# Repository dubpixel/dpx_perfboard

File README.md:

<!-- Improved compatibility of back to top link: See: https://github.com/othneildrew/Best-README-Template/pull/73 -->

<!--
*** Thanks for checking out the Best-README-Template. If you have a suggestion
*** that would make this better, please fork the repo and create a pull request
*** or simply open an issue with the tag "enhancement".
*** Don't forget to give the project a star!
*** Thanks again! Now go create something AMAZING! :D

*** /// d   u   b   p   i   x   e   l  ---  f   o   r   k   ////--
*** this has additionally been modifed by @dubpixel for hardware use
*** search dpx_perfboard.. search & replace is COMMAND OPTION F
*** 
*** todo: want to add reflections seciton, upload as github template.  - done 12.9
*** todo: backport to blank template - done 12.9**
*** todo add small product image thats not in a details tag
*** figure out how to get the details tag to properly render in jekyll for gihub pages.

-->

<!-- PROJECT SHIELDS -->
<!--
*** I'm using markdown "reference style" links for readability.
*** Reference links are enclosed in brackets [ ] instead of parentheses ( ).
*** See the bottom of this document for the declaration of the reference variables
*** for contributors-url, forks-url, etc. This is an optional, concise syntax you may use.
*** https://www.markdownguide.org/basic-syntax/#reference-style-links
***
-->
[![Contributors][contributors-shield]][contributors-url]
[![Forks][forks-shield]][forks-url]
[![Stargazers][stars-shield]][stars-url]
[![Issues][issues-shield]][issues-url]
[![MIT License][license-shield]][license-url]
[![LinkedIn][linkedin-shield]][linkedin-url]

<!-- PROJECT LOGO -->
<br />
<div align="center">

<h1 align="center">dpx_perfboard</h1>
<h3 align="center"><i>_yes... it comes in black!_</i></h3>
<br />
  <p align="center">
    ...an open source kicad protoboard in various sizes for whatever!
        <br />
    <p align="center">
     <a href="https://github.com/dubpixel/dpx_perfboard/tree/main/"><strong>Project Here!</strong></a>
     »  
    <a href="https://github.com/dubpixel/dpx_perfboard/tree/main/src/bom"><strong>BOM Here!</strong></a>
     » 
    <a href="https://dubpixel.github.io/dpx_perfboard/ebom/index.html"><strong>Interactive BOM Here!</strong></a>
     <br />
    <a href="https://github.com/dubpixel/dpx_perfboard/issues/new?labels=bug&template=bug-report---.md">Report Bug</a>
    ·
    <a href="https://github.com/dubpixel/dpx_perfboard/issues/new?labels=enhancement&template=feature-request---.md">Request Feature</a>
    </div>
    </p>
</div>
   <br />
<!-- TABLE OF CONTENTS -->
<details>
  <summary>Table of Contents</summary>
  <ol>
    <li>
      <a href="#about-the-project">About The Project</a>
      <ul>
        <li><a href="#built-with">Built With</a></li>
      </ul>
    </li>
    <li>
      <a href="#getting-started">Getting Started</a>
      <ul>
        <li><a href="#prerequisites">Prerequisites</a></li>
        <li><a href="#installation">Installation</a></li>
      </ul>
    </li>
    <li><a href="#usage">Usage</a></li>    
    <li><a href="#reflection">Reflection</a></li>
    <li><a href="#roadmap">Roadmap</a></li>
    <li><a href="#contributing">Contributing</a></li>
    <li><a href="#license">License</a></li>
    <li><a href="#contact">Contact</a></li>
    <li><a href="#acknowledgments">Acknowledgments</a></li>
  </ol>
</details>
    <br />
<!-- ABOUT THE PROJECT -->
</div>

## About The Project
i needed to have a perfboard spacing to test in kicad for another project so naturally i decided to just finish it off. Nice to have some dpx perfboards with added busses, our logo, and all black .

author(s): // www.dubpixel.tv  - i@dubpixel.tv | other authors

<details>
  <summary>Images</summary>
  
### 05x10+SMT 
![FRONT][product-a]

### 05x15
![FRONT][product-b]

### 05x30-split
![FRONT][product-c]

</details>

<p align="right">(<a href="#readme-top">back to top</a>)</p>

### Built With 
 * [![KiCad][KiCad.org]][KiCad-url]
<!--
  
 * [![Fusion360][Fusion-360]][Autodesk-url]
 * [![Next][Next.js]][Next-url]
 * [![React][React.js]][React-url]
 * [![Vue][Vue.js]][Vue-url]
 * [![Angular][Angular.io]][Angular-url]
 * [![Svelte][Svelte.dev]][Svelte-url]
 * [![Laravel][Laravel.com]][Laravel-url]
 * [![Bootstrap][Bootstrap.com]][Bootstrap-url]
 * [![JQuery][JQuery.com]][JQuery-url]
 
-->
<p align="right">(<a href="#readme-top">back to top</a>)</p>

<!-- GETTING STARTED -->
## Getting Started

### Prerequisites

### Installation

1. Download...
2. Enjoy.
3. Repeat as Needed!

<p align="right">(<a href="#readme-top">back to top</a>)</p>

<!-- USAGE EXAMPLES -->
## Usage

<!-- Use this space to show useful examples of how a project can be used. Additional screenshots, code examples and demos work well in this space. You may also link to more resources.

_For more examples, please refer to the [Documentation](https://example.com)_-->

<p align="right">(<a href="#readme-top">back to top</a>)</p>

## Reflection
<!-- 
* what did we learn? 
* what do we like/hate?
* what would/could we do differently? 
-->

<p align="right">(<a href="#readme-top">back to top</a>)</p>

<!-- ROADMAP -->

## Roadmap

- [ ] Feature 1
    - [ ] Nested Feature

See the [open issues](https://github.com/dubpixel/dpx_perfboard/issues) for a full list of proposed features (and known issues).

<p align="right">(<a href="#readme-top">back to top</a>)</p>

<!-- CONTRIBUTING -->
## Contributing

Contributions are what make the open source community such an amazing place to learn, inspire, and create. Any contributions you make are **greatly appreciated**.

If you have a suggestion that would make this better, please fork the repo and create a pull request. You can also simply open an issue with the tag "enhancement".
Don't forget to give the project a star! Thanks again!

1. Fork the Project
2. Create your Feature Branch (`git checkout -b feature/AmazingFeature`)
3. Commit your Changes (`git commit -m 'Add some AmazingFeature'`)
4. Push to the Branch (`git push origin feature/AmazingFeature`)
5. Open a Pull Request

<p align="right">(<a href="#readme-top">back to top</a>)</p>

### Top contributors:

<!-- LICENSE -->
## License

  Distributed under the UNLICENSE License. See `LICENSE.txt` for more information.

<p align="right">(<a href="#readme-top">back to top</a>)</p>

<!-- CONTACT -->
## Contact

  ### Joshua Fleitell - i@dubpixel.tv

  Project Link: [https://github.com/dubpixel/dpx_perfboard](https://github.com/dubpixel/dpx_perfboard)

<p align="right">(<a href="#readme-top">back to top</a>)</p>

<!-- ACKNOWLEDGMENTS -->
## Acknowledgments

<!--
  *  - the best !
-->

<p align="right">(<a href="#readme-top">back to top</a>)</p>

<!-- MARKDOWN LINKS & IMAGES -->
<!-- https://www.markdownguide.org/basic-syntax/#reference-style-links -->
[contributors-shield]: https://img.shields.io/github/contributors/dubpixel/dpx_perfboard.svg?style=for-the-badge
[contributors-url]: https://github.com/dubpixel/dpx_perfboard/graphs/contributors
[forks-shield]: https://img.shields.io/github/forks/gdubpixel/dpx_perfboard.svg?style=for-the-badge
[forks-url]: https://github.com/dubpixel/dpx_perfboard/network/members
[stars-shield]: https://img.shields.io/github/stars/dubpixel/dpx_perfboard.svg?style=for-the-badge
[stars-url]: https://github.com/dubpixel/dpx_perfboard/stargazers
[issues-shield]: https://img.shields.io/github/issues/dubpixel/dpx_perfboard.svg?style=for-the-badge
[issues-url]: https://github.com/dubpixel/dpx_perfboard/issues
[license-shield]: https://img.shields.io/github/license/dubpixel/dpx_perfboard.svg?style=for-the-badge
[license-url]: https://github.com/dubpixel/dpx_perfboard/blob/master/LICENSE.txt
[linkedin-shield]: https://img.shields.io/badge/-LinkedIn-black.svg?style=for-the-badge&logo=linkedin&colorB=555
[linkedin-url]: https://linkedin.com/in/jfleitell
[product-screenshot]: images/screenshot.png
[product-front]: images/front.png
[product-rear]: images/rear.png
[product-pcbFront]: images/pcb_front.png
[product-pcbRear]: images/pcb_rear.png
[product-a]: images/5x10.png
[product-b]: images/5x15.png
[product-c]: images/5x30s.png
[Next.js]: https://img.shields.io/badge/next.js-000000?style=for-the-badge&logo=nextdotjs&logoColor=white
[Next-url]: https://nextjs.org/
[React.js]: https://img.shields.io/badge/React-20232A?style=for-the-badge&logo=react&logoColor=61DAFB
[React-url]: https://reactjs.org/
[Vue.js]: https://img.shields.io/badge/Vue.js-35495E?style=for-the-badge&logo=vuedotjs&logoColor=4FC08D
[Vue-url]: https://vuejs.org/
[Angular.io]: https://img.shields.io/badge/Angular-DD0031?style=for-the-badge&logo=angular&logoColor=white
[Angular-url]: https://angular.io/
[Svelte.dev]: https://img.shields.io/badge/Svelte-4A4A55?style=for-the-badge&logo=svelte&logoColor=FF3E00
[Svelte-url]: https://svelte.dev/
[Laravel.com]: https://img.shields.io/badge/Laravel-FF2D20?style=for-the-badge&logo=laravel&logoColor=white
[Laravel-url]: https://laravel.com
[Bootstrap.com]: https://img.shields.io/badge/Bootstrap-563D7C?style=for-the-badge&logo=bootstrap&logoColor=white
[Bootstrap-url]: https://getbootstrap.com
[JQuery.com]: https://img.shields.io/badge/jQuery-0769AD?style=for-the-badge&logo=jquery&logoColor=white
[JQuery-url]: https://jquery.com 
[KiCad.org]: https://img.shields.io/badge/KiCad-v8.0.6-blue
[KiCad-url]: https://kicad.org 
[Fusion-360]: https://img.shields.io/badge/Fusion360-v4.2.0-green
[Autodesk-url]: https://autodesk.com

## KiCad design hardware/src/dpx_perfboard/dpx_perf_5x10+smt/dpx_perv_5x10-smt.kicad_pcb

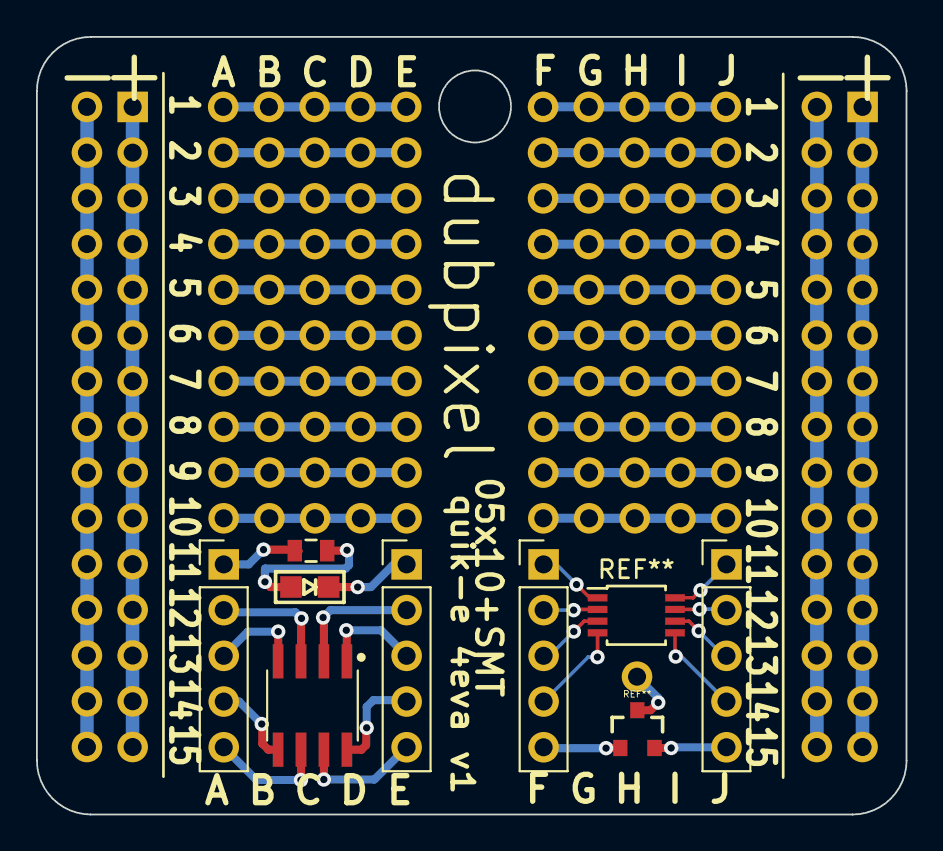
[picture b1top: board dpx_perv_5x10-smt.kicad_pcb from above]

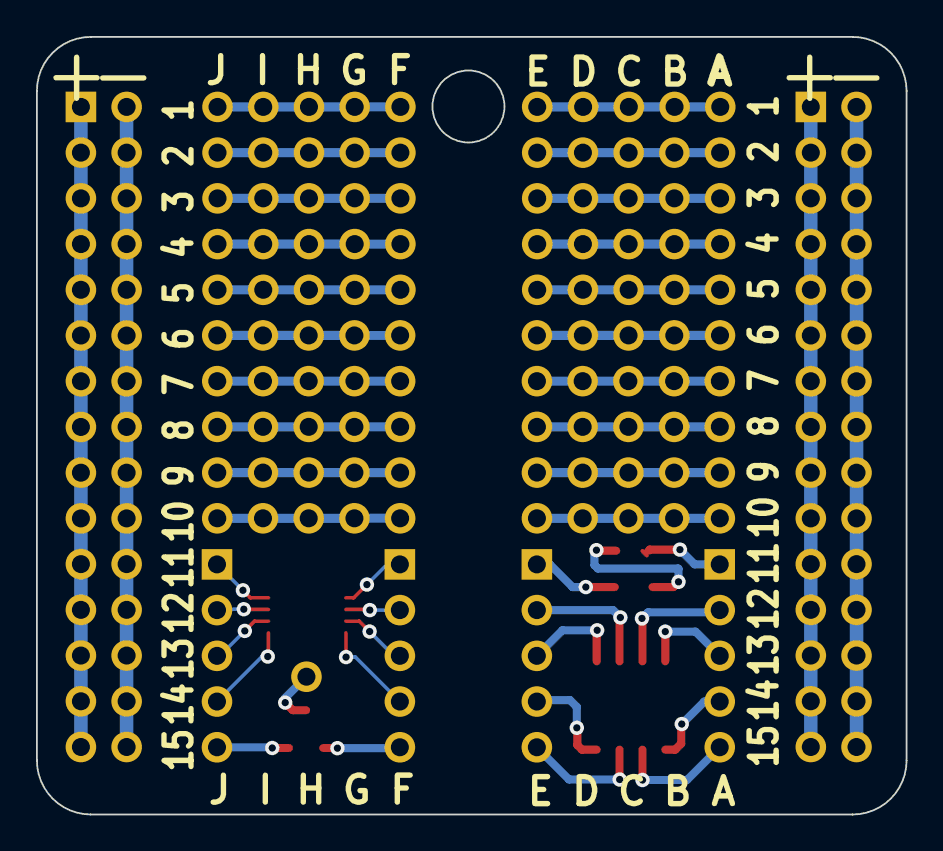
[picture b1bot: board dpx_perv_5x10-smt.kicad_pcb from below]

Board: 4 copper layers, 48.3 x 43.2 mm, 5 parts (2 on the bottom side), 2 nets.

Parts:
1: SOIC127P600X144-8
J1: Conn_02x10_Top_Bottom; dpx-02x15-nosilk
J2: Conn_02x30_Top_Bottom; dpx-02x15-nosilk
U1, U2: DPX_PROTOBOARD-5x5

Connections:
GND: J1.2, J1.4, J1.6, J1.8, J1.10, J1.12, J1.14, J1.16, J1.18, J1.20, J2.2, J2.4, J2.6, J2.8, J2.10, J2.12, J2.14, J2.16, J2.18, J2.20
VCC: J1.1, J1.3, J1.5, J1.7, J1.9, J1.11, J1.13, J1.15, J1.17, J1.19, J2.1, J2.3, J2.5, J2.7, J2.9, J2.11, J2.13, J2.15, J2.17, J2.19

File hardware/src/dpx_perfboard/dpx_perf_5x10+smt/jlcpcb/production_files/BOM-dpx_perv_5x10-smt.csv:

Comment,Designator,Footprint,LCSC
Conn_02x10_Top_Bottom,J1,dpx-02x15-nosilk,
Conn_02x30_Top_Bottom,J2,dpx-02x15-nosilk,
~,U2,DPX_PROTOBOARD-5x5,
~,U1,DPX_PROTOBOARD-5x5,

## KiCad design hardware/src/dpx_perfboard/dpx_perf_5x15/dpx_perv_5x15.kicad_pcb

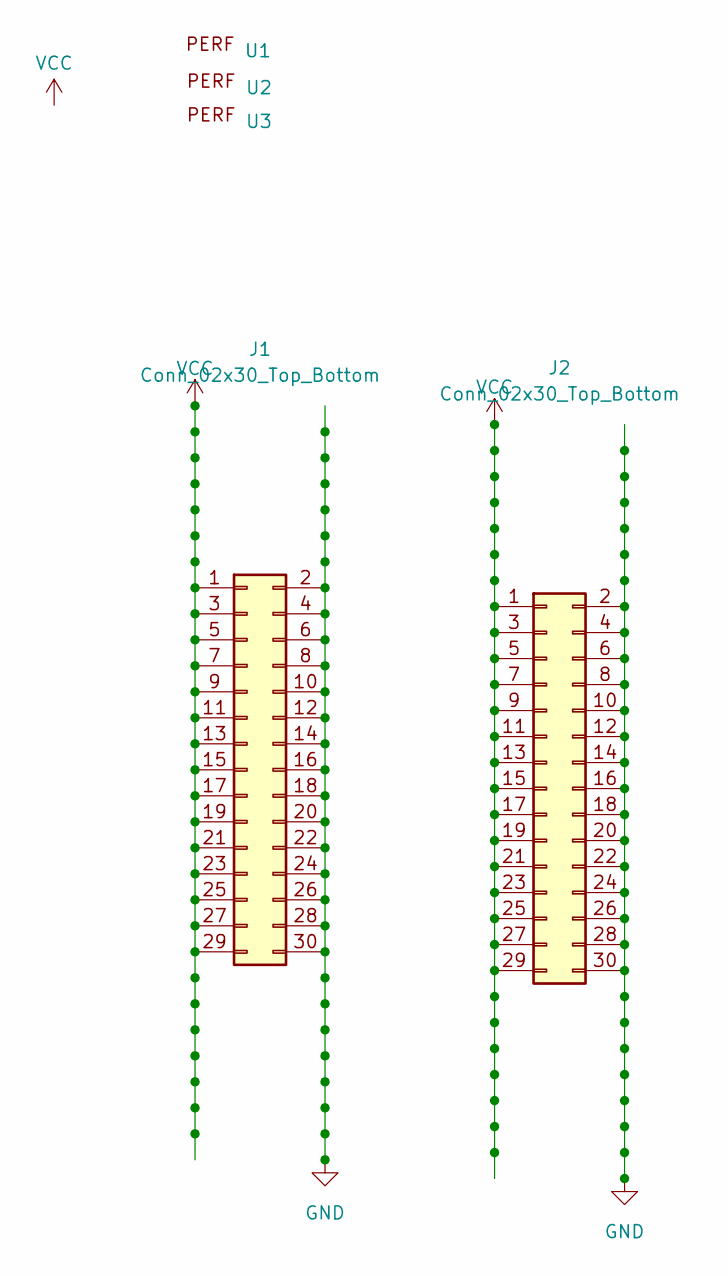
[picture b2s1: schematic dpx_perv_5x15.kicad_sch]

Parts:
J1, J2: Conn_02x30_Top_Bottom; dpx-02x15-nosilk
U1, U2, U3: DPX_PROTOBOARD-5x5

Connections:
GND: J1.2, J1.4, J1.6, J1.8, J1.10, J1.12, J1.14, J1.16, J1.18, J1.20, J1.22, J1.24, J1.26, J1.28, J1.30, J2.2, J2.4, J2.6, J2.8, J2.10, J2.12, J2.14, J2.16, J2.18, J2.20, J2.22, J2.24, J2.26, J2.28, J2.30
VCC: J1.1, J1.3, J1.5, J1.7, J1.9, J1.11, J1.13, J1.15, J1.17, J1.19, J1.21, J1.23, J1.25, J1.27, J1.29, J2.1, J2.3, J2.5, J2.7, J2.9, J2.11, J2.13, J2.15, J2.17, J2.19, J2.21, J2.23, J2.25, J2.27, J2.29

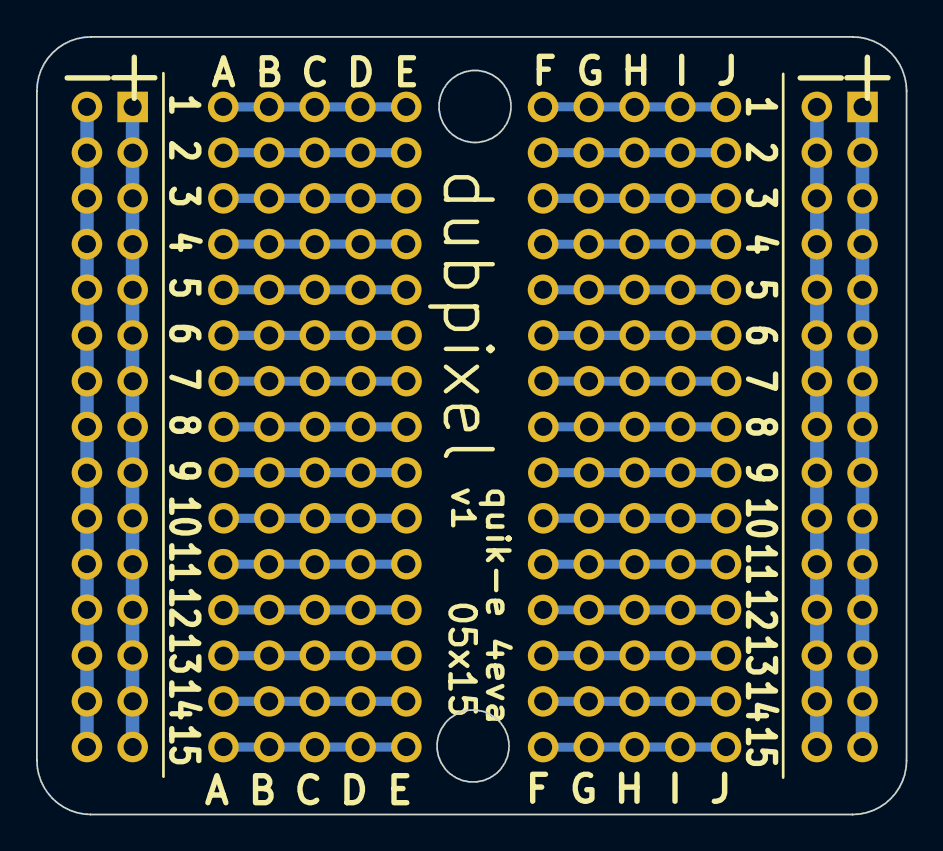
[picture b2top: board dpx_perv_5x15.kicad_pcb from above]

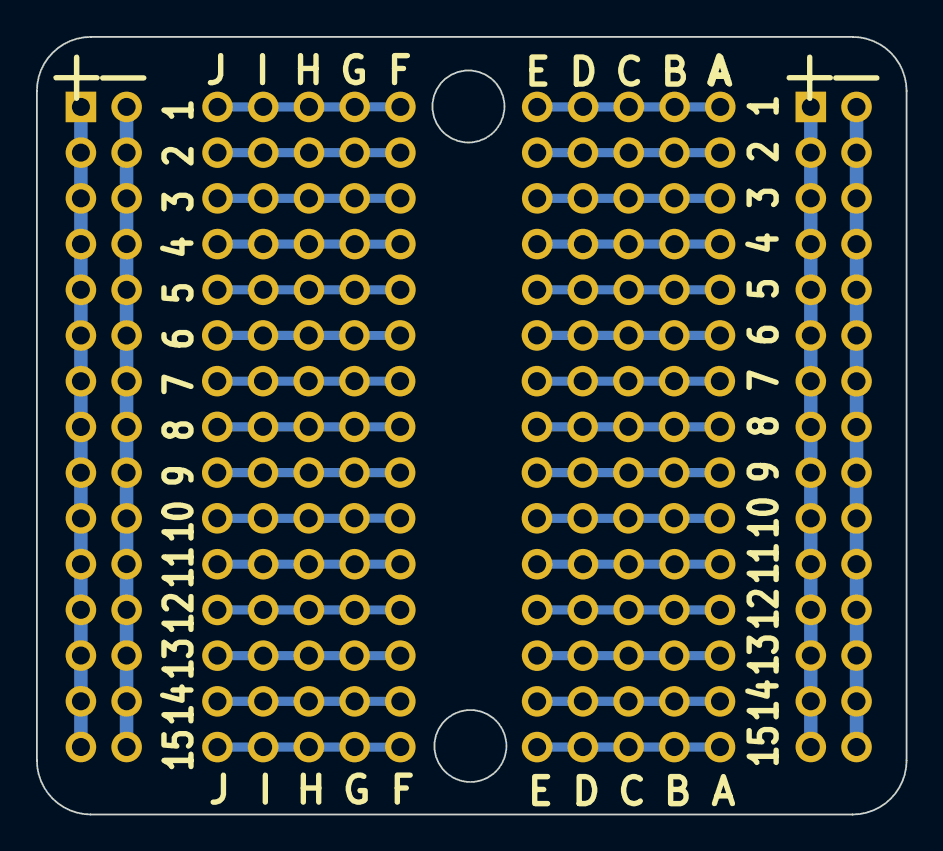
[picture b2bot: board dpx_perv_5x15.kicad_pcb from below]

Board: 4 copper layers, 48.3 x 43.2 mm, 5 parts (3 on the bottom side), 2 nets.

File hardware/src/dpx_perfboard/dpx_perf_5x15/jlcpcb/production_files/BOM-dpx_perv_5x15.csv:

Comment,Designator,Footprint,LCSC
Conn_02x30_Top_Bottom,J1,dpx-02x15-nosilk,
Conn_02x30_Top_Bottom,J2,dpx-02x15-nosilk,
~,U2,DPX_PROTOBOARD-5x5,
~,U1,DPX_PROTOBOARD-5x5,
~,U3,DPX_PROTOBOARD-5x5,

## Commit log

2024-12-10 images and such
2024-12-10 more images
2024-12-10 update filename
